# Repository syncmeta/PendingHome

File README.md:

<h1 align="center">PendingHome</h1>

<p align="center">
  全屋双色温灯光控制方案
</p>

<p align="center">

</p>
这个仓库是一个方案说明文档的形式，提供一个大概思路。

这目前是设想中的方案，还未落地，因为水电还没弄好，卡住了。

仓库的大头目前是灯光控制板的设计。这类东西现成产品要么太贵，要么不符合要求，而且设计起来对AI来说算不上特别特别难的事情。按照设计预期，这块板应该能带动24V 12A 6路双色温的LED灯。设计完之后拿去嘉立创打样。

## 仓库内容

| 目录 | 是什么 |
|---|---|
| [`ha-home/`](ha-home/) | 主力 HA 部署：台式机跑 Debian + Docker，含一套能造出**开机自配置**系统镜像的脚本，以及 Zigbee 接入的现场排障记录 |
| [`ha-t630/`](ha-t630/) | 惠普 t630 瘦客户机做 HA 主机的部署，以及 HA + Scrypted 把大华摄像头接进 HomeKit（含 HKSV） |
| [`ha-lab/`](ha-lab/) | Mac 上的 Lima 虚拟机试验台。`ha-home` 就是从它平移过来的，现已退役 |
| [`sensor-nodes/`](sensor-nodes/) | ESP32-C3 传感器节点的 ESPHome 固件（CO₂、光谱、门窗磁），含选购清单 |
| [`docs/`](docs/) | 跨项目的设计文档 |
| [`cct-driver/`](cct-driver/) | 6 路 CCT 灯驱动板：KiCad 工程、生产文件、ESPHome 固件、验板清单 |

顶层的 `t630-*.sh` 是给 t630 那台机器做裸机引导（USB 直连 / PXE）的 Mac 侧脚本。

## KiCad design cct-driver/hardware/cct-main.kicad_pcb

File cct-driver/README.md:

# cct-driver

6 通道 CCT（色温可调）LED 灯带驱动板 —— 24V 输入、单板 12A 连续设计，ESP32 + ESPHome，
接入 Home Assistant。用户零焊接：贴片与插件件全部由嘉立创代焊，收到即成品。

| 目录 | 内容 |
|---|---|
| `hardware/` | KiCad 工程、生产文件（Gerber / BOM / 坐标）、亚克力外壳切割图、各版改板脚本 |
| `firmware/` | ESPHome 配置（`cct-driver.yaml` 正式板、`cct-driver-devboard.yaml` 开发板） |
| `docs/` | 设计规格书与实施计划 |

> 这块板子原来是一个独立仓库，2026-08-23 连同全部提交历史并进了 PendingHome，
> 现在是它的一个子目录。原仓库 <https://github.com/syncmeta/cct-driver> 保留为归档，
> 不再更新；合库时提交哈希做过重写，本文与脚本里提到的旧哈希指的是那边的。

## 上手

```sh
git clone https://github.com/syncmeta/PendingHome.git
cd PendingHome
git config core.hooksPath .githooks     # ← 必做，见下一节
cd cct-driver
```

**`git config core.hooksPath .githooks` 这一句不能漏**（在仓库根执行，不是在本目录）。
Git 的钩子不随仓库克隆自动生效，不执行这句，下面那个防护就是摆设。

**下文所有命令都在 `cct-driver/` 目录下执行**，除非另有说明。

改板脚本要用 KiCad 自带的 Python（系统 `python3` 里没有 `pcbnew`）：

```sh
/Applications/KiCad/KiCad.app/Contents/Frameworks/Python.framework/Versions/Current/bin/python3 hardware/gen_xxx.py
```

## ⚠️ KiCad 工程文件会被 GUI 悄悄重置

**这个坑踩过一次，而且是静默的 —— 不会报错，不会提示，只有 diff 里看得见。**

用 KiCad 图形界面打开本工程后，`hardware/cct-main.kicad_pro` 里的这些东西可能被重置成出厂默认：

- 5 个网络类（`Default` / `TRUNK` / `PWR2` / `PWR1` / `GND`）被砍成只剩 `Default`
- 14 条 `netclass_patterns`（把 `V24_*`、`CH*_VOUT`、`GND` 等网络分配到各类的规则）被清空
- `Default` 的 `track_width` 从 0.25 掉到 0.2、`min_text_height` 从 0.5 变成 0.8

**危害**：板子已经布完线，铜箔的实际线宽不受影响，**这一版生产文件是安全的**。但之后任何一次改板，
DRC 都会按错误的规则跑 —— 主电流脊椎按 3.5mm 设计的走线，会被当成 0.2mm 的普通线校验，
真正的问题反而查不出来。

**排查结论**（2026-08-11）：不是脚本干的，也不是 KiCad 10 的格式迁移有问题。
对照实验证明，用无头 `pcbnew` 走一遍 `LoadBoard` + `SaveBoard`，
`net_settings` 从 v4 迁到 v5 是**完全无损**的，5 个类和 14 条规则一条不少。
真凶是图形界面那一侧（旁证：只有 GUI 会写的 `cct-main.kicad_prl` 同时被改了）。

**防护**：`hardware/check-netclasses.py` 断言这些值仍是基准值，
经仓库根的 `.githooks/pre-commit` 在每次提交前自动跑。

**检查失败时该怎么办**：

```sh
# 情况一（绝大多数）：你并没有故意改这些设置，是 GUI 干的 —— 直接退回
git checkout -- hardware/cct-main.kicad_pro

# 情况二：你确实有意调整了网络类/设计规则 —— 同步更新脚本里的基准值，别绕过检查
$EDITOR hardware/check-netclasses.py
```

**不要用 `git commit --no-verify` 糊弄过去。** 这个检查存在的唯一理由，
就是这类改动看起来人畜无害、而代价要到下一次改板才显形。

**用 GUI 前后的习惯**：开之前确认 `cct-main.kicad_pro` 已提交（工作区干净），
关掉之后 `git diff hardware/cct-main.kicad_pro` 看一眼再决定要不要留。

## ⚠️ 料号只有一个源头：`gen_sch.py`

`hardware/gen_sch.py` 里的 `part(位号, C编号, {引脚: 网络})` 表是**全工程唯一的料号出处** ——
`gen_bom.py` 直接解析它来出 BOM。板文件里每个封装虽然也带一份 Value 字段，但那只是
`F.Fab` 层上给人看的文字，**不进任何出货 Gerber，也没有任何一步会自动更新它**。

改完料号请顺手跑这两条：

```bash
KP=/Applications/KiCad/KiCad.app/Contents/Frameworks/Python.framework/Versions/Current/bin/python3
$KP hardware/gen_sync_values.py     # 把板文件 Value 同步成 gen_sch.py 里的真实料号
$KP hardware/gen_sch.py             # 重新生成原理图（顺便验证生成器还跑得动）
```

**为什么专门写这一条**：2026-08-07 把 6 个精密电阻 + 1 个 C0G 电容换成真实料号时，
只改了 `gen_sch.py`。结果 ——

- `gen_sch.py` 从那天起**一跑就报「库缺失 7 个」**（那 7 个料号的符号没下进符号库），
  也就是说**原理图整整六天没法重新生成，而且没人发现** —— 因为没有任何一步会去碰它；
- 板文件里那 7 个 Value 停在旧料号，重新生成原理图时 KiCad 的 schematic-parity
  会逐个报 `Value (R62) doesn't match symbol value`。

两件都已修好（符号别名表 + `gen_sync_values.py`）。**`gen_sch.py` 能不能跑通，
本身就是一个健康检查** —— 改完原理图相关的东西，跑一次它，比什么都省事。

> 📌 `--check` 模式只报告不写盘：`$KP hardware/gen_sync_values.py --check`，
> 适合提交前自检。

## 生产文件

> ⚠️ **传出去之前先跑这一条:**
> ```bash
> python3 hardware/check-outputs-fresh.py
> ```
> 它检查 Gerber / CPL / BOM / 渲染图有没有比板文件旧。**2026-08-13 那天板子改了三轮,
> 出货包一次都没跟上** —— 每一轮都仔细验了 DRC 和网表,却差点把停在三个提交之前的
> 包和写着旧料号的 BOM 传去下单。靠人记是记不住的,所以写成检查。

> 📌 **封装里那个 `LCSC Part` 属性不是料号,别读它。** 它是 `easyeda2kicad` 下载封装时
> 记下的**来源**——比如所有 0603 电阻共用一个从 `C21190` 下载来的 `R0603` 封装,于是
> R18(实为 `C25804` 10k)的 `LCSC Part` 就写着 `C21190`。195 个封装里有 80 个对不上,
> **这是正常的**。料号只有一个源头:`gen_sch.py` 的 part 表(见上一节)。
> (v1.1 可以考虑把这个属性整批删掉,免得再有人误读;它不进任何出货文件,不急。)

下单用的三个文件都在 `hardware/`：

| 文件 | 用途 |
|---|---|
| `cct-main-gerber.zip` | Gerber |
| `bom-jlc.csv` | BOM（嘉立创格式） |
| `cpl-jlc.csv` | 元件坐标（嘉立创格式） |

下单前逐项核对 `hardware/order-checklist.md` —— 里面记着表面工艺、阻焊颜色、
容易选错的料号等一批会咬人的地方。

## 收到板子之后

照 **`docs/bring-up-checklist.md`** 从头打勾执行 —— 从开测前要买什么，到上电前量阻抗、
仅 USB 刷固件、24V 空载、12A 满载热测、人为短路验保险丝，最后到「什么条件下才能放行
剩下 3 片」。每一项都写了用什么表、点哪个测试点、读到多少算过、不过了怎么办
（全部不需要动烙铁）。**器材要提前几天买，第 0 章就是采购清单。**

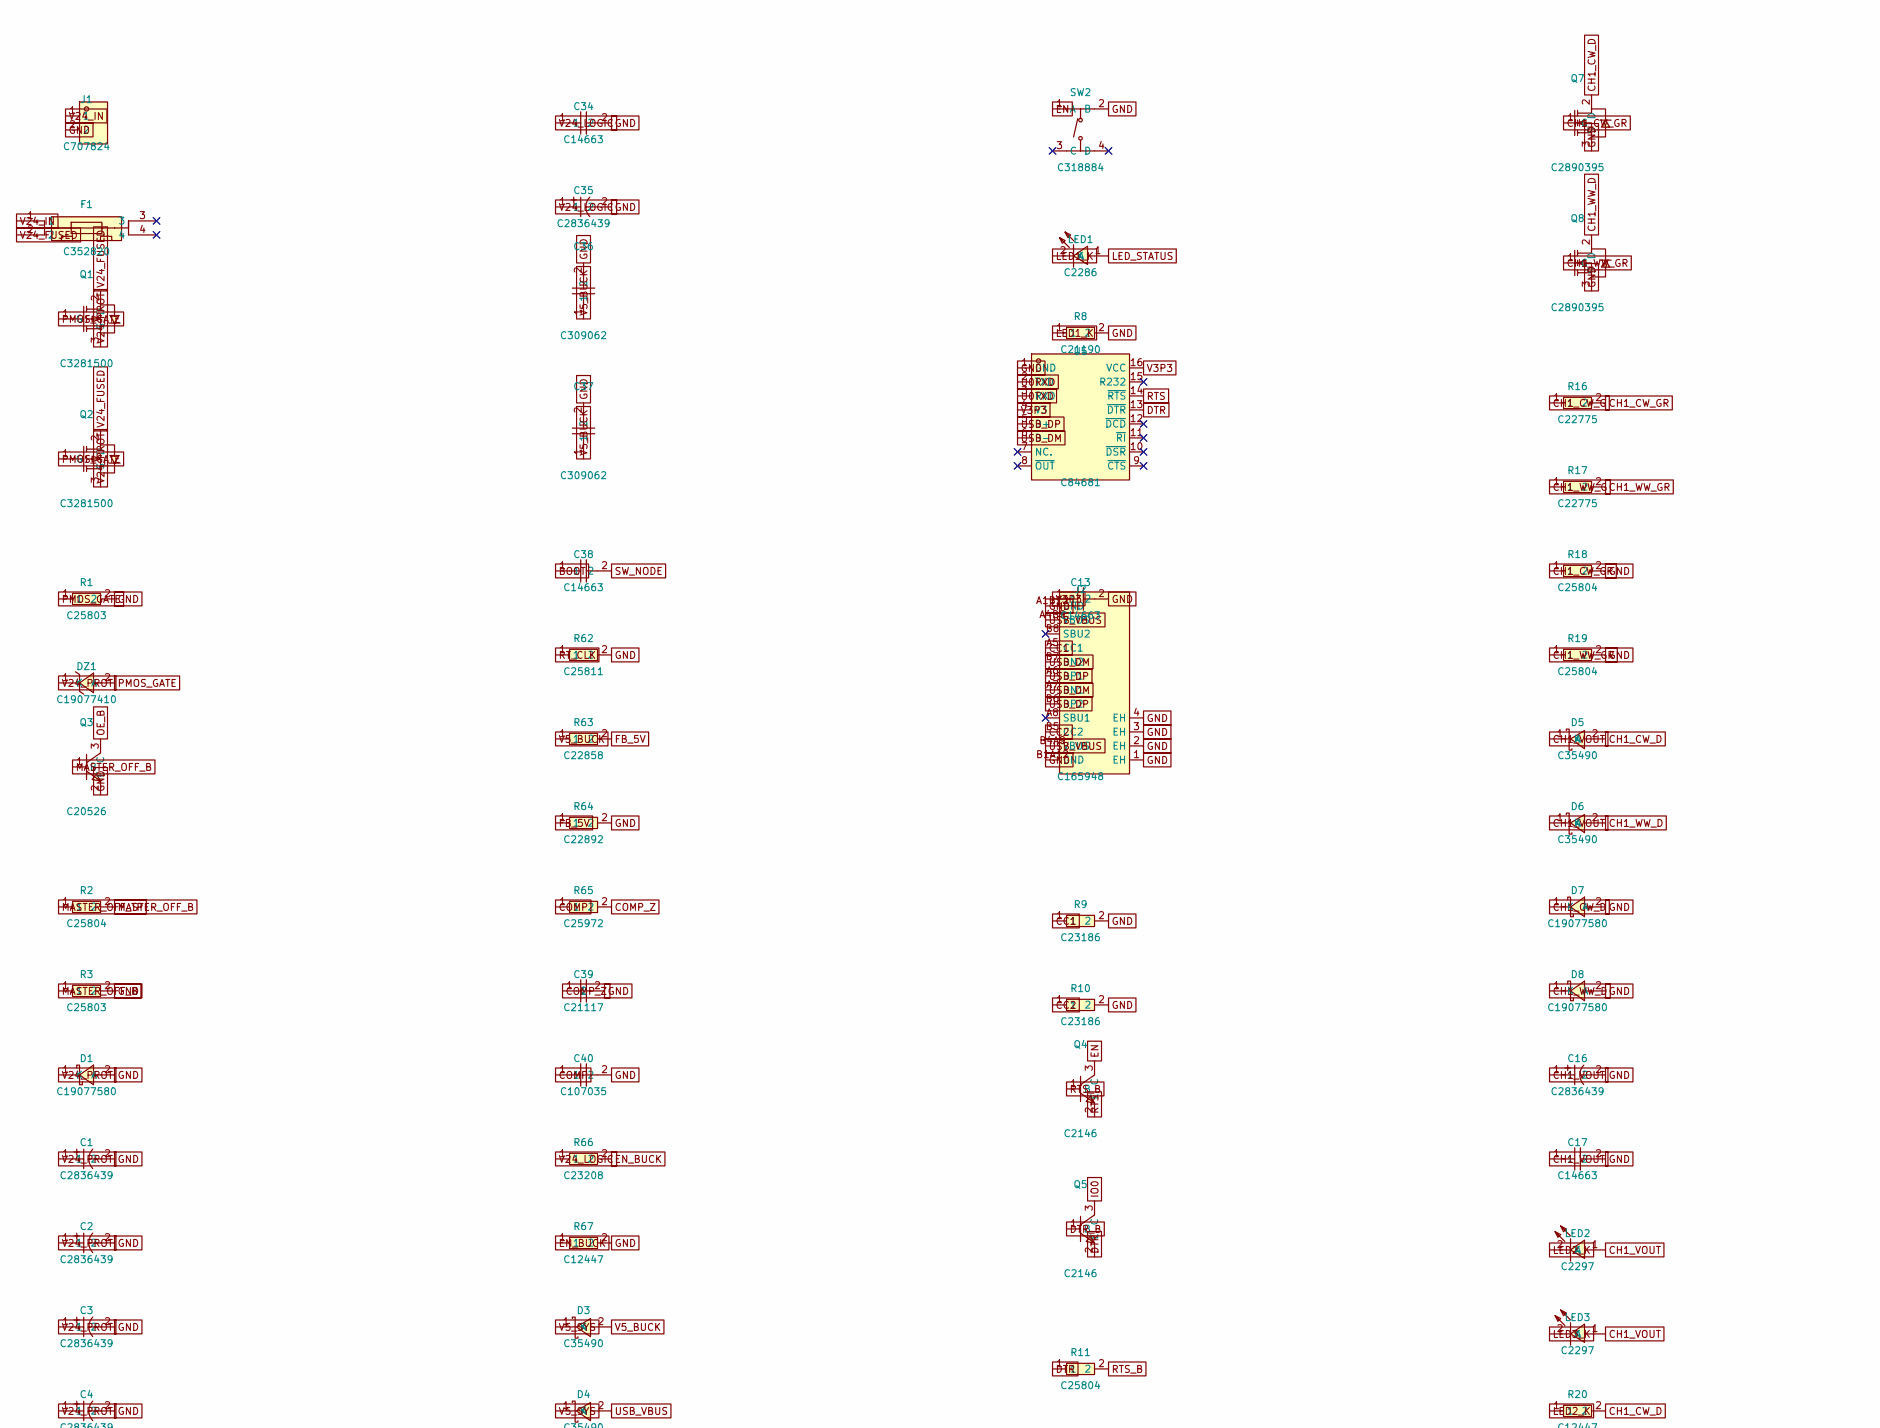
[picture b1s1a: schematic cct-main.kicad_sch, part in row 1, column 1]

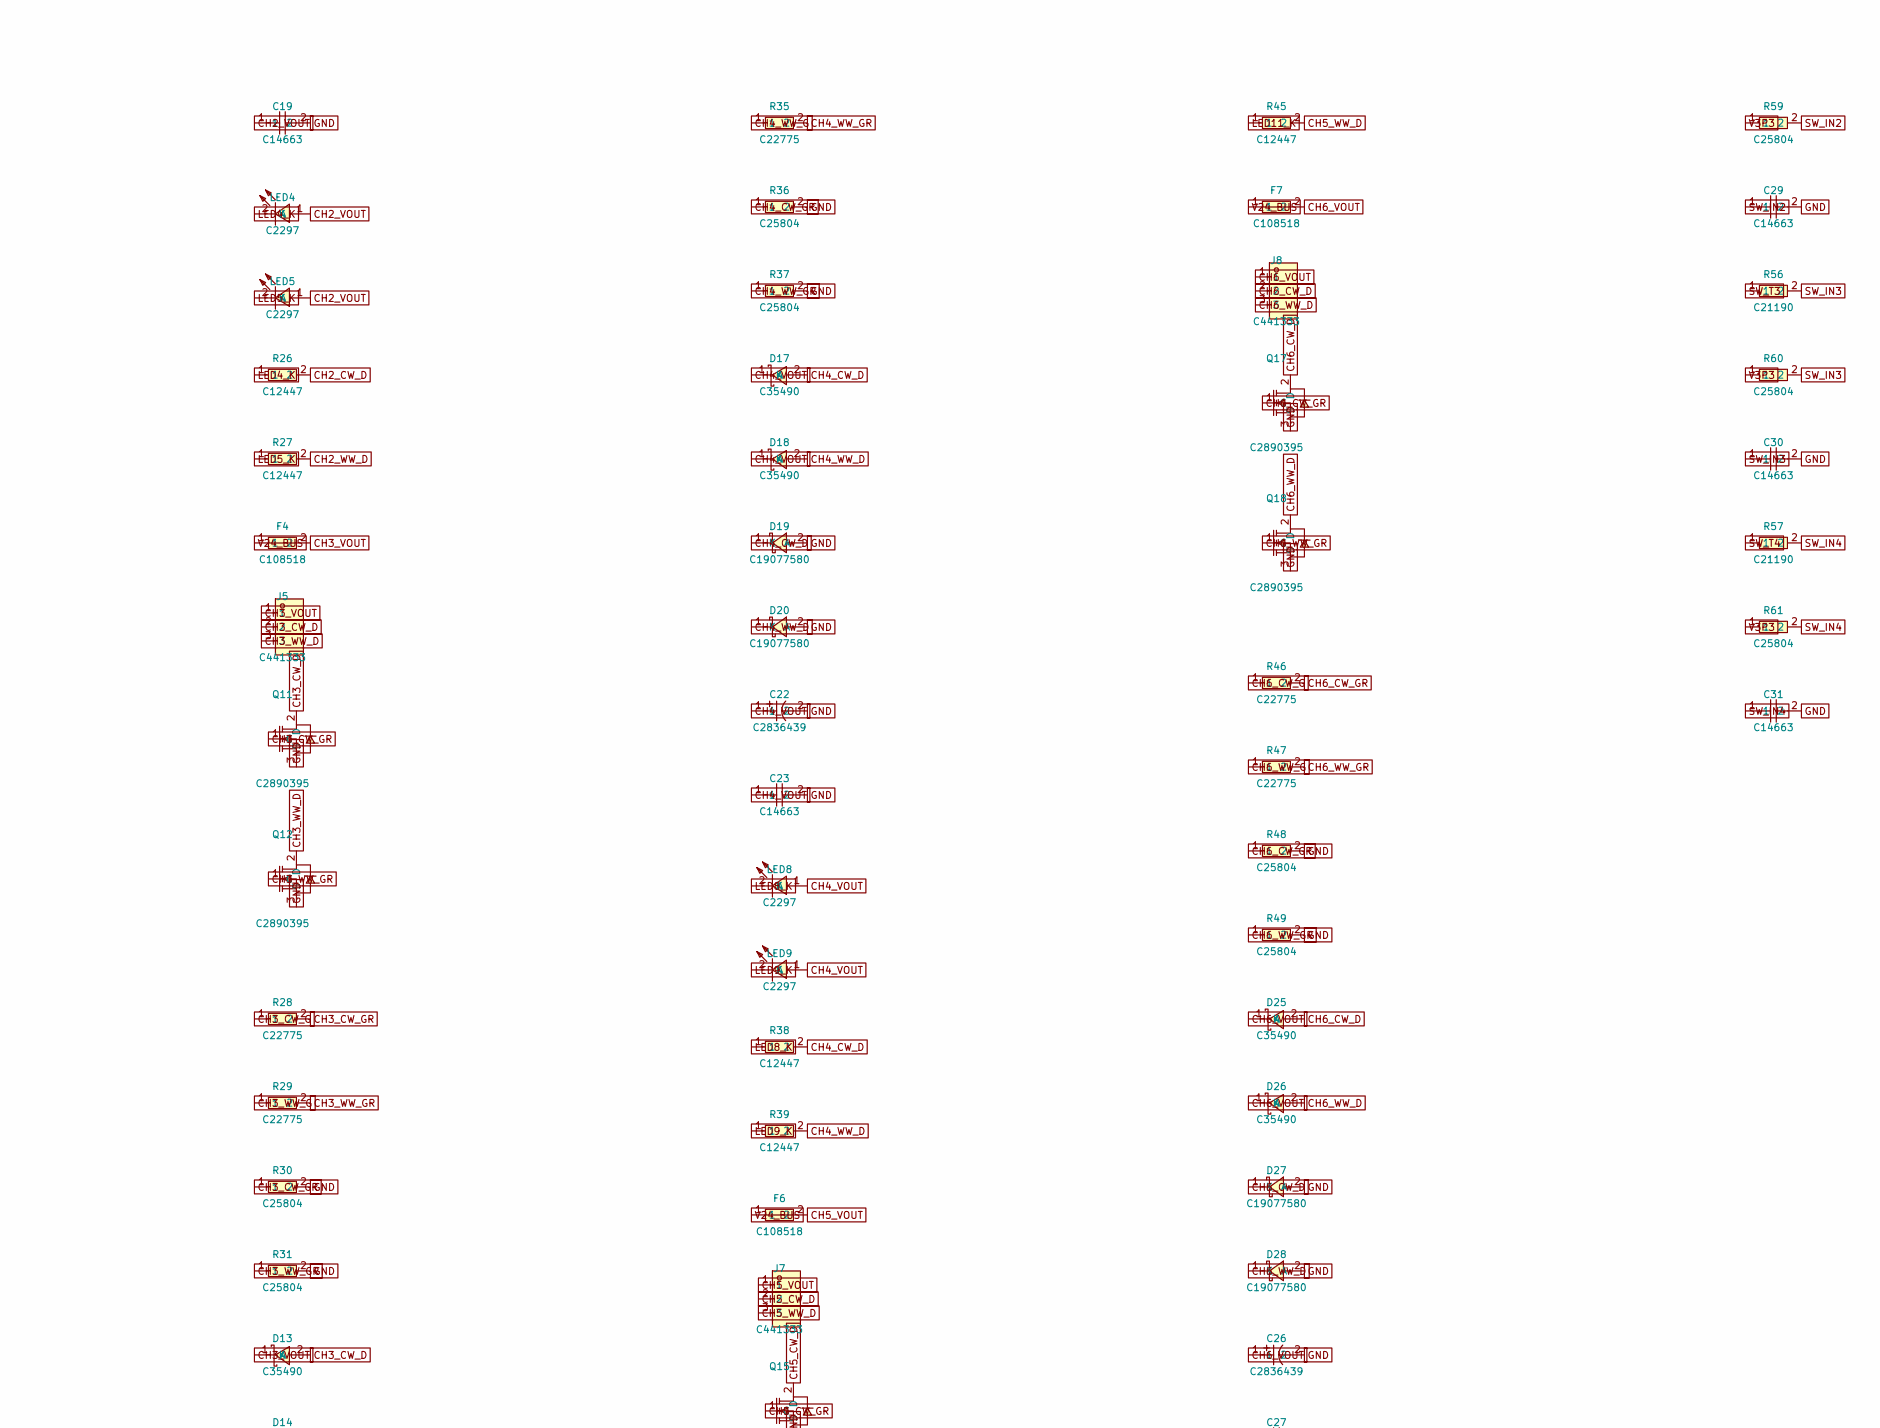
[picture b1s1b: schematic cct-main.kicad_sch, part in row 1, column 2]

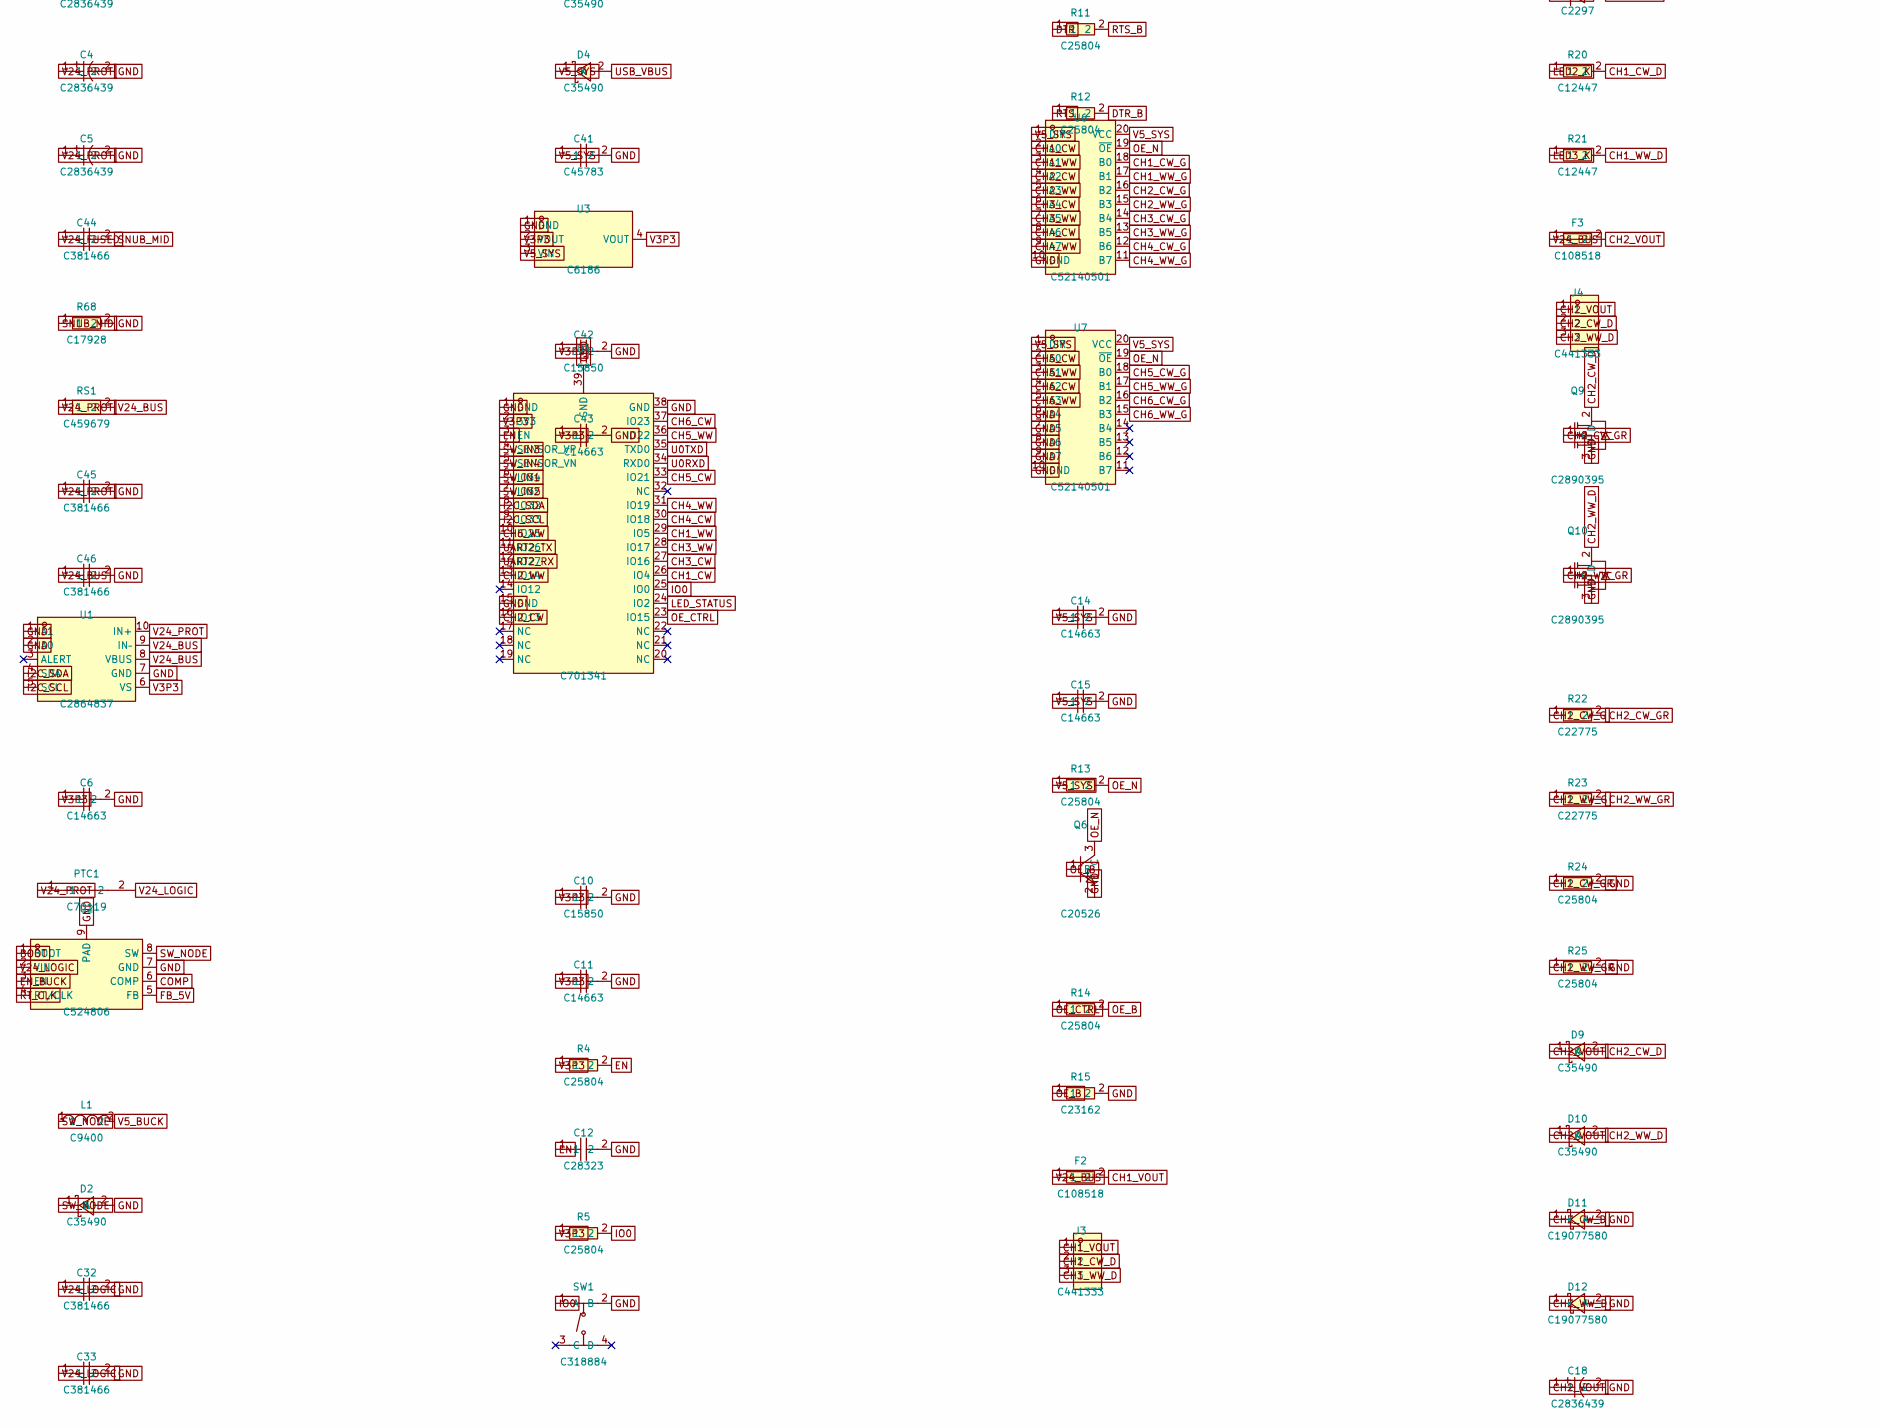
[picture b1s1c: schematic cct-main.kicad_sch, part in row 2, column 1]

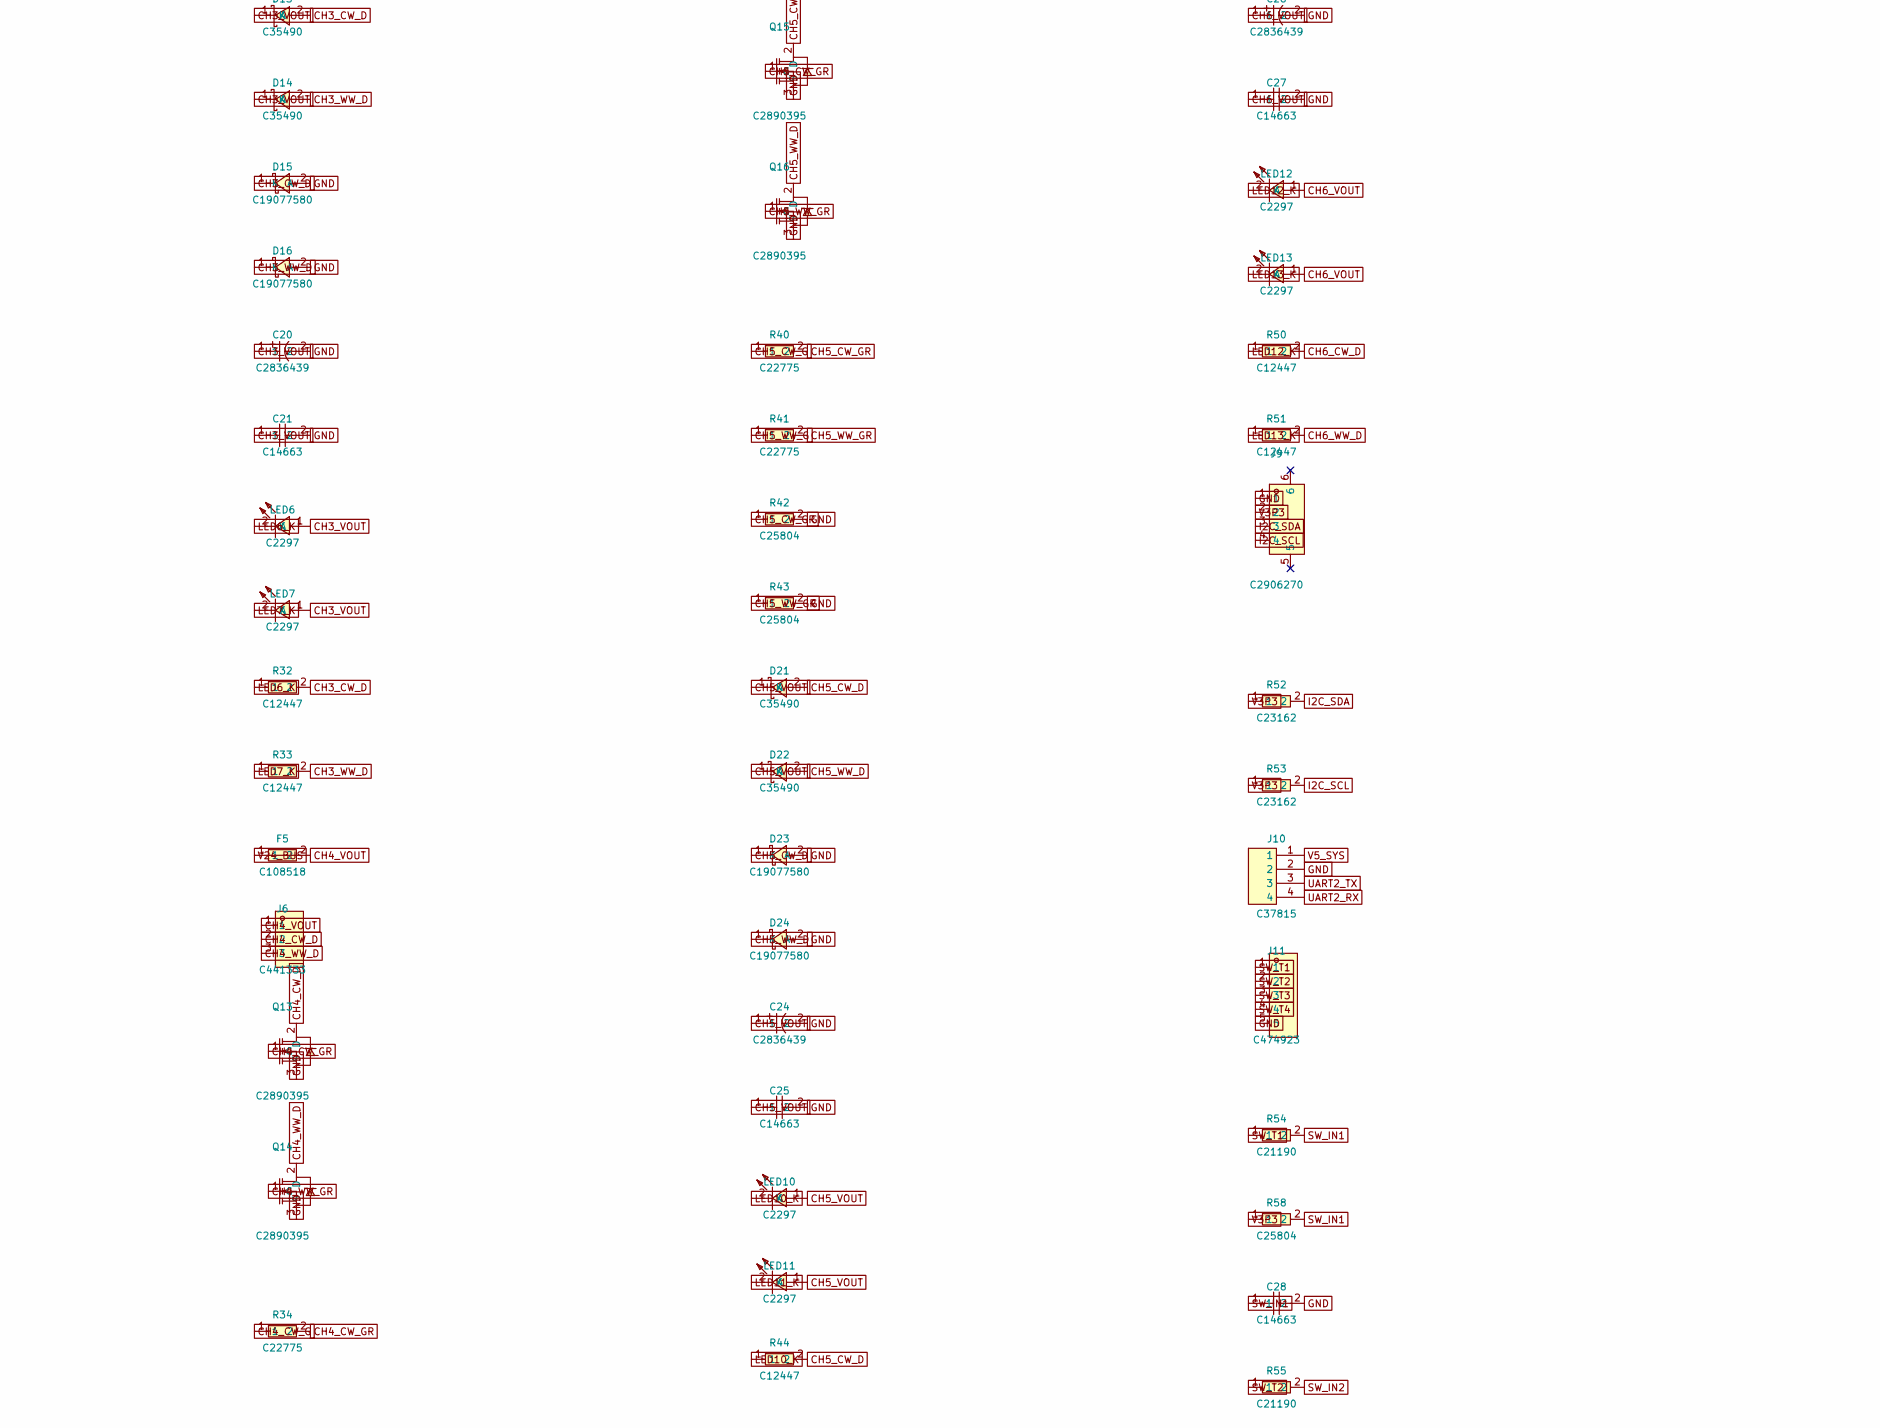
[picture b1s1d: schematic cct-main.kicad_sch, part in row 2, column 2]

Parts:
C1, C2, C3, C4, C5, C16, C18, C20, C22, C24, C26, C35: C2836439
C6, C11, C13, C14, C15, C17, C19, C21, C23, C25, C27, C28, C29, C30, C31, C34, C38, C43: C14663
C10, C42: C15850
C12: C28323
C32, C33, C44, C45, C46: C381466
C36, C37: C309062
C39: C21117
C40: C107035
C41: C45783
D1, D7, D8, D11, D12, D15, D16, D19, D20, D23, D24, D27, D28: C19077580
D2, D3, D4, D5, D6, D9, D10, D13, D14, D17, D18, D21, D22, D25, D26: C35490
DZ1: C19077410
F1: C352820
F2, F3, F4, F5, F6, F7: C108518
J1: C707824
J2: C165948
J3, J4, J5, J6, J7, J8: C441333
J9: C2906270
J10: C37815
J11: C474923
L1: C9400
LED1: C2286
LED2, LED3, LED4, LED5, LED6, LED7, LED8, LED9, LED10, LED11, LED12, LED13: C2297
PTC1: C70119
Q1, Q2: C3281500
Q3, Q6: C20526
Q4, Q5: C2146
Q7, Q8, Q9, Q10, Q11, Q12, Q13, Q14, Q15, Q16, Q17, Q18: C2890395
R1, R3: C25803
R2, R4, R5, R11, R12, R13, R14, R18, R19, R24, R25, R30, R31, R36, R37, R42, R43, R48, R49, R58, R59, R60, R61: C25804
R8, R54, R55, R56, R57: C21190
R9, R10: C23186
R15, R52, R53: C23162
R16, R17, R22, R23, R28, R29, R34, R35, R40, R41, R46, R47: C22775
R20, R21, R26, R27, R32, R33, R38, R39, R44, R45, R50, R51, R67: C12447
R62: C25811
R63: C22858
R64: C22892
R65: C25972
R66: C23208
R68: C17928
RS1: C459679
SW1, SW2: C318884
U1: C2864837
U2: C524806
U3: C6186
U4: C701341
U5: C84681
U6, U7: C52140501

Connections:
BOOT: C38.1, U2.1 (BOOT)
CC1: J2.A5 (CC1), R9.1
CC2: J2.B5 (CC2), R10.1
CH1_CW: U4.26 (IO4), U6.2 (A0)
CH1_CW_D: D5.2 (A), D7.1 (K), J3.2, Q7.2 (D), R20.2
CH1_CW_G: R16.1, U6.18 (B0)
CH1_CW_GR: Q7.1 (G), R16.2, R18.1
CH1_VOUT: C16.1, C17.1, D5.1 (K), D6.1 (K), F2.2, J3.1, LED2.1 (A), LED3.1 (A)
CH1_WW: U4.29 (IO5), U6.3 (A1)
CH1_WW_D: D6.2 (A), D8.1 (K), J3.3, Q8.2 (D), R21.2; also elsewhere on the board
CH1_WW_G: R17.1, U6.17 (B1)
CH1_WW_GR: Q8.1 (G), R17.2, R19.1; also elsewhere on the board
CH2_CW: U4.16 (IO13), U6.4 (A2)
CH2_CW_D: D9.2 (A), D11.1 (K), J4.2, Q9.2 (D), R26.2
CH2_CW_G: R22.1, U6.16 (B2)
CH2_CW_GR: Q9.1 (G), R22.2, R24.1
CH2_VOUT: C18.1, C19.1, D9.1 (K), D10.1 (K), F3.2, J4.1, LED4.1 (A), LED5.1 (A)
CH2_WW: U4.13 (IO14), U6.5 (A3)
CH2_WW_D: D10.2 (A), D12.1 (K), J4.3, Q10.2 (D), R27.2
CH2_WW_G: R23.1, U6.15 (B3)
CH2_WW_GR: Q10.1 (G), R23.2, R25.1
CH3_CW: U4.27 (IO16), U6.6 (A4)
CH3_CW_D: D13.2 (A), D15.1 (K), J5.2, Q11.2 (D), R32.2
CH3_CW_G: R28.1, U6.14 (B4)
CH3_CW_GR: Q11.1 (G), R28.2, R30.1
CH3_VOUT: C20.1, C21.1, D13.1 (K), D14.1 (K), F4.2, J5.1, LED6.1 (A), LED7.1 (A)
CH3_WW: U4.28 (IO17), U6.7 (A5)
CH3_WW_D: D14.2 (A), D16.1 (K), J5.3, Q12.2 (D), R33.2
CH3_WW_G: R29.1, U6.13 (B5)
CH3_WW_GR: Q12.1 (G), R29.2, R31.1
CH4_CW: U4.30 (IO18), U6.8 (A6)
CH4_CW_D: D17.2 (A), D19.1 (K), J6.2, Q13.2 (D), R38.2
CH4_CW_G: R34.1, U6.12 (B6)
CH4_CW_GR: Q13.1 (G), R34.2, R36.1
CH4_VOUT: C22.1, C23.1, D17.1 (K), D18.1 (K), F5.2, J6.1, LED8.1 (A), LED9.1 (A)
CH4_WW: U4.31 (IO19), U6.9 (A7)
CH4_WW_D: D18.2 (A), D20.1 (K), J6.3, Q14.2 (D), R39.2
CH4_WW_G: R35.1, U6.11 (B7)
CH4_WW_GR: Q14.1 (G), R35.2, R37.1
CH5_CW: U4.33 (IO21), U7.2 (A0)
CH5_CW_D: D21.2 (A), D23.1 (K), J7.2, Q15.2 (D), R44.2
CH5_CW_G: R40.1, U7.18 (B0)
CH5_CW_GR: Q15.1 (G), R40.2, R42.1
CH5_VOUT: C24.1, C25.1, D21.1 (K), D22.1 (K), F6.2, J7.1, LED10.1 (A), LED11.1 (A)
CH5_WW: U4.36 (IO22), U7.3 (A1)
CH5_WW_D: D22.2 (A), D24.1 (K), J7.3, Q16.2 (D), R45.2
CH5_WW_G: R41.1, U7.17 (B1)
CH5_WW_GR: Q16.1 (G), R41.2, R43.1
CH6_CW: U4.37 (IO23), U7.4 (A2)
CH6_CW_D: D25.2 (A), D27.1 (K), J8.2, Q17.2 (D), R50.2
CH6_CW_G: R46.1, U7.16 (B2)
CH6_CW_GR: Q17.1 (G), R46.2, R48.1
CH6_VOUT: C26.1, C27.1, D25.1 (K), D26.1 (K), F7.2, J8.1, LED12.1 (A), LED13.1 (A)
CH6_WW: U4.10 (IO25), U7.5 (A3)
CH6_WW_D: D26.2 (A), D28.1 (K), J8.3, Q18.2 (D), R51.2
CH6_WW_G: R47.1, U7.15 (B3)
CH6_WW_GR: Q18.1 (G), R47.2, R49.1
COMP: C40.1, R65.1, U2.6 (COMP)
COMP_Z: C39.1, R65.2
DTR: Q5.2 (E), R11.1, U5.13 (~DTR)
DTR_B: Q5.1 (B), R12.2
EN: C12.1, Q4.3 (C), R4.2, SW2.1 (A), U4.3 (EN)
EN_BUCK: R66.2, R67.1, U2.3 (EN)
FB_5V: R63.2, R64.1, U2.5 (FB)
GND: C1.2, C2.2, C3.2, C4.2, C5.2, C6.2, C10.2, C11.2, C12.2, C13.2, C14.2, C15.2, C16.2, C17.2, C18.2, C19.2, C20.2, C21.2, C22.2, C23.2, C24.2, C25.2, C26.2, C27.2, C28.2, C29.2, C30.2, C31.2, C32.2, C33.2, C34.2, C35.2, C36.2, C37.2, C39.2, C40.2, C41.2, C42.2, C43.2, C45.2, C46.2, D1.2 (A), D2.2 (A), D7.2 (A), D8.2 (A), D11.2 (A), D12.2 (A), D15.2 (A), D16.2 (A), D19.2 (A), D20.2 (A), D23.2 (A), D24.2 (A), D27.2 (A), D28.2 (A), J1.2, J2.1 (EH), J2.2 (EH), J2.3 (EH), J2.4 (EH), J2.A1B12 (GND), J2.B1A12 (GND), J9.1, J10.2, J11.5, Q3.2 (E), Q6.2 (E), Q7.3 (S), Q8.3 (S), Q9.3 (S), Q10.3 (S), Q11.3 (S), Q12.3 (S), Q13.3 (S), Q14.3 (S), Q15.3 (S), Q16.3 (S), Q17.3 (S), Q18.3 (S), R1.2, R3.2, R8.2, R9.2, R10.2, R15.2, R18.2, R19.2, R24.2, R25.2, R30.2, R31.2, R36.2, R37.2, R42.2, R43.2, R48.2, R49.2, R62.2, R64.2, R67.2, R68.2, SW1.2 (B), SW2.2 (B), U1.1 (A1), U1.2 (A0), U1.7 (GND), U2.7 (GND), U2.9 (PAD), U3.1 (GND), U4.1 (GND), U4.15 (GND), U4.38 (GND), U4.39 (GND), U5.1 (GND), U6.10 (GND), U7.6 (A4), U7.7 (A5), U7.8 (A6), U7.9 (A7), U7.10 (GND); also elsewhere on the board
I2C_SCL: J9.4, R53.2, U1.5 (SCL), U4.9 (IO33)
I2C_SDA: J9.3, R52.2, U1.4 (SDA), U4.8 (IO32)
IO0: Q5.3 (C), R5.2, SW1.1 (A), U4.25 (IO0)
LED1_K: LED1.2 (K), R8.1
LED2_K: LED2.2 (K), R20.1
LED3_K: LED3.2 (K), R21.1
LED4_K: LED4.2 (K), R26.1
LED5_K: LED5.2 (K), R27.1
LED6_K: LED6.2 (K), R32.1
LED7_K: LED7.2 (K), R33.1
LED8_K: LED8.2 (K), R38.1
LED9_K: LED9.2 (K), R39.1
LED10_K: LED10.2 (K), R44.1
LED11_K: LED11.2 (K), R45.1
LED12_K: LED12.2 (K), R50.1
LED13_K: LED13.2 (K), R51.1
LED_STATUS: LED1.1 (A), U4.24 (IO2)
MASTER_OFF_B: Q3.1 (B), R2.2, R3.1
MASTER_OFF_TP: R2.1; also elsewhere on the board
OE_B: Q3.3 (C), Q6.1 (B), R14.2, R15.1
OE_CTRL: R14.1, U4.23 (IO15)
OE_N: Q6.3 (C), R13.2, U6.19 (~OE), U7.19 (~OE)
PMOS_GATE: DZ1.2 (A), Q1.1 (G), Q2.1 (G), R1.1; also elsewhere on the board
RTS: Q4.2 (E), R12.1, U5.14 (~RTS)
RTS_B: Q4.1 (B), R11.2
RT_CLK: R62.1, U2.4 (RT/CLK)
SNUB_MID: C44.2, R68.1
SW_IN1: C28.1, R54.2, R58.2, U4.6 (IO34)
SW_IN2: C29.1, R55.2, R59.2, U4.7 (IO35)
SW_IN3: C30.1, R56.2, R60.2, U4.4 (SENSOR_VP)
SW_IN4: C31.1, R57.2, R61.2, U4.5 (SENSOR_VN)
SW_NODE: C38.2, D2.1 (K), L1.1, U2.8 (SW)
SW_T1: J11.1, R54.1
SW_T2: J11.2, R55.1
SW_T3: J11.3, R56.1
SW_T4: J11.4, R57.1
U0RXD: U4.34 (RXD0), U5.2 (TXD)
U0TXD: U4.35 (TXD0), U5.3 (RXD)
UART2_RX: J10.4, U4.12 (IO27)
UART2_TX: J10.3, U4.11 (IO26)
USB_DM: J2.A7 (DN1), J2.B7 (DN2), U5.6 (D-)
USB_DP: J2.A6 (DP1), J2.B6 (DP2), U5.5 (D+)
USB_VBUS: D4.2 (A), J2.A4B9 (VBUS), J2.B4A9 (VBUS)
V3P3: C6.1, C10.1, C11.1, C13.1, C42.1, C43.1, J9.2, R4.1, R5.1, R52.1, R53.1, R58.1, R59.1, R60.1, R61.1, U1.6 (VS), U3.2 (VOUT), U3.4 (VOUT), U4.2 (3V3), U5.4 (V3), U5.16 (VCC); also elsewhere on the board
V5_BUCK: C36.1, C37.1, D3.2 (A), L1.2, R63.1
V5_SYS: C14.1, C15.1, C41.1, D3.1 (K), D4.1 (K), J10.1, R13.1, U3.3 (VIN), U6.1 (DIR), U6.20 (VCC), U7.1 (DIR), U7.20 (VCC); also elsewhere on the board
V24_BUS: C46.1, F2.1, F3.1, F4.1, F5.1, F6.1, F7.1, RS1.2, U1.8 (VBUS), U1.9 (IN–); also elsewhere on the board
V24_FUSED: C44.1, F1.2, Q1.2 (D), Q2.2 (D)
V24_IN: F1.1, J1.1
V24_LOGIC: C32.1, C33.1, C34.1, C35.1, PTC1.2, R66.1, U2.2 (VIN)
V24_PROT: C1.1, C2.1, C3.1, C4.1, C5.1, C45.1, D1.1 (K), DZ1.1 (K), PTC1.1, Q1.3 (S), Q2.3 (S), RS1.1, U1.10 (IN+)

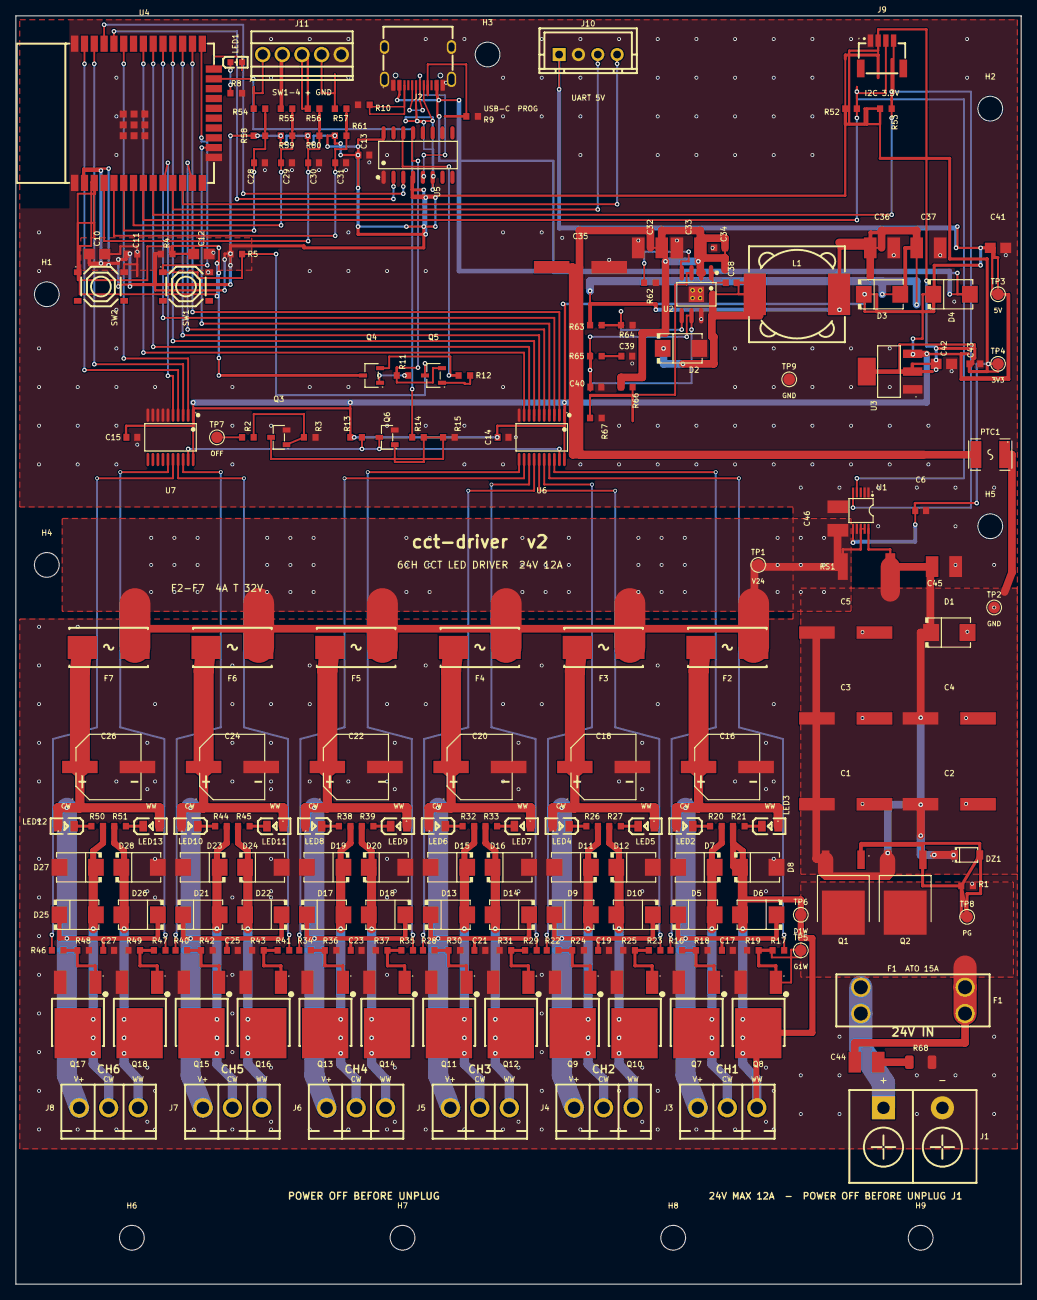
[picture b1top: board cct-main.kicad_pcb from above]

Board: 2 copper layers, 130.0 x 164.0 mm, 217 parts (0 on the bottom side), 116 nets.

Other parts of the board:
H1, H2, H3, H4, H5, H6, H7, H8, H9: M3; MountingHole_3.2mm_M3
TP1: V24_BUS; TestPoint_Pad_D1.5mm
TP2, TP9: GND; TestPoint_Pad_D1.5mm
TP3: V5_SYS; TestPoint_Pad_D1.5mm
TP4: V3P3; TestPoint_Pad_D1.5mm
TP5: CH1_WW_GR; TestPoint_Pad_D1.5mm
TP6: CH1_WW_D; TestPoint_Pad_D1.5mm
TP7: MASTER_OFF_TP; TestPoint_Pad_D1.5mm
TP8: PMOS_GATE; TestPoint_Pad_D1.5mm

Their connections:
CH1_WW_D: TP6.1; also elsewhere on the board
CH1_WW_GR: TP5.1; also elsewhere on the board
GND: TP2.1, TP9.1; also elsewhere on the board
MASTER_OFF_TP: TP7.1; also elsewhere on the board
PMOS_GATE: TP8.1; also elsewhere on the board
V3P3: TP4.1; also elsewhere on the board
V5_SYS: TP3.1; also elsewhere on the board
V24_BUS: TP1.1; also elsewhere on the board

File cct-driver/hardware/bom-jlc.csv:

Comment,Designator,Footprint,LCSC Part #
120pF/50V C0G 0603(C_pole),C40,C0603,C107035
Nano2 保险丝座(配 4A 慢断 C99551),"F2,F3,F4,F5,F6,F7",FUSE-SMD_L9.8-W5.0_01550900M,C108518
40.2kΩ 0603,"R20,R21,R26,R27,R32,R33,R38,R39,R44,R45,R50,R51,R67",R0603,C12447
100nF 0603,"C6,C11,C13,C14,C15,C17,C19,C21,C23,C25,C27,C28,C29,C30,C31,C34,C38,C43",C0603,C14663
10µF/25V 0805,"C10,C42",C0805,C15850
Type-C 16P 贴板式,J2,USB-C_SMD-TYPE-C-31-M-12_1,C165948
"1Ω ±1% 1206(阻尼电阻,起始值)",R68,R1206,C17928
BZT52C12 12V 稳压管 SOD-123,DZ1,SOD-123_L2.7-W1.6-LS3.7-RD,C19077410
SMBJ26A TVS,"D1,D7,D8,D11,D12,D15,D16,D19,D20,D23,D24,D27,D28",SMB_L4.6-W3.6-LS5.3-RD,C19077580
MMBT3904 NPN(总断路电平转换),"Q3,Q6",SOT-23-3_L2.9-W1.3-P1.90-LS2.4-BR,C20526
33nF/50V X7R 0603(C_comp),C39,C0603,C21117
1kΩ 0603,"R8,R54,R55,R56,R57",R0603,C21190
S8050 SOT-23,"Q4,Q5",SOT-23-3_L3.0-W1.7-P0.95-LS2.9-BR,C2146
100Ω 0603 栅阻,"R16,R17,R22,R23,R28,R29,R34,R35,R40,R41,R46,R47",R0603,C22775
102kΩ ±1% 0603(R_hi),R63,R0603,C22858
红 0603,LED1,0603,C2286
18.2kΩ ±1% 0603(R_lo),R64,R0603,C22892
翠绿 0805,"LED2,LED3,LED4,LED5,LED6,LED7,LED8,LED9,LED10,LED11,LED12,LED13",0805,C2297
4.7kΩ 0603,"R15,R52,R53",R0603,C23162
5.1kΩ 0603,"R9,R10",R0603,C23186
590kΩ ±1% 0603(UVLO1),R66,R0603,C23208
100kΩ 0603,"R1,R3",R0603,C25803
10kΩ 0603(Q3 基极串阻),"R2,R4,R5,R11,R12,R13,R14,R18,R19,R24,R25,R30,R31,R36,R37,R42,R43,R48,R49,R58,R59,R60,R61",R0603,C25804
200kΩ ±1% 0603(R_T),R62,R0603,C25811
4.75kΩ ±1% 0603(R_comp),R65,R0603,C25972
1µF/50V X7R 0805(上电复位延时),C12,C0805,C28323
C2836439,"C1,C2,C3,C4,C5,C16,C18,C20,C22,C24,C26,C35",CAP-SMD_BD8.0-L8.3-W8.3-LS9.3-FD,C2836439
INA237AIDGSR VSSOP-10,U1,VSSOP-10_L3.0-W3.0-P0.50-LS4.9-BL,C2864837
UMW 20N06 TO-252,"Q7,Q8,Q9,Q10,Q11,Q12,Q13,Q14,Q15,Q16,Q17,Q18",TO-252-2_L6.6-W6.1-P4.57-LS10.1-BL-1,C2890395
Qwiic JST-SH 1.0mm 4P 卧贴,J9,CONN-SMD_4P-P1.00_SHOU-HAN_1.0-4P-WT,C2906270
22µF/25V X7R 1210 ×2,"C36,C37",C1210,C309062
TS-1187A 轻触开关,"SW1,SW2",SW-SMD_4P-L5.1-W5.1-P3.70-LS6.5-TL_H1.5,C318884
SQD50P06-15L-GE3 P-MOS,"Q1,Q2",TO-252-2_L6.6-W6.1-P4.58-LS9.9-BR,C3281500
Keystone 3557-2 双联 ATO 保险丝座,F1,FUSE-TH_4P-L19.8-W6.7_3557-2,C352820
SS36B 续流 SMB,"D2,D3,D4,D5,D6,D9,D10,D13,D14,D17,D18,D21,D22,D25,D26",SMB_L4.6-W3.6-LS5.3-RD,C35490
XH2.54-4P 立式,J10,CONN-TH_4P-P2.50_XH-4A,C37815
4.7µF/100V X7R 1210,"C32,C33,C44,C45,C46",C1210,C381466
KF2EDGV-3.81-3P 针座,"J3,J4,J5,J6,J7,J8",CONN-TH_3P-P3.81_KF2EDGV-3.81-3P,C441333
22µF/25V 0805,C41,C0805,C45783
2mΩ ±1% 3W 2512 合金采样电阻,RS1,R2512,C459679
KF128-2.54-5P 端子,J11,CONN-TH_5P-P2.54_KF128-2.54-5P,C474923
74HCT245PW TSSOP-20,"U6,U7",TSSOP-20_L6.5-W4.4-P0.65-LS6.4-BL,C52140501
TPS54360BDDAR HSOIC-8 PowerPAD,U2,SOIC-8_L5.0-W4.0-P1.27-LS6.0-BL-EP2.0,C524806
AMS1117-3.3 SOT-223,U3,SOT-223-3_L6.5-W3.4-P2.30-LS7.0-BR,C6186
mSMD110-33V 1.1A/33V 1812,PTC1,F1812,C70119
ESP32-WROOM-32E-N4,U4,WIFI-SMD_ESP32-WROOM-32E,C701341
KF7.62-2P 输入端子(24A),J1,CONN-TH_KF7.62-2P,C707824
CH340C SOP-16,U5,SOP-16_L10.0-W3.9-P1.27-LS6.0-BL,C84681
"33µH,Isat ≥5.5A,DCR 65mΩ,12.3×12.3mm",L1,IND-SMD_L12.3-W12.3,C9400
无需采购,"H1,H2,H3,H4,H5,H6,H7,H8,H9",MountingHole_3.2mm_M3,
测试焊盘,"TP1,TP2,TP3,TP4,TP5,TP6,TP7,TP8,TP9",TestPoint_Pad_D1.5mm,

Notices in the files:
README.md:
License: MIT
